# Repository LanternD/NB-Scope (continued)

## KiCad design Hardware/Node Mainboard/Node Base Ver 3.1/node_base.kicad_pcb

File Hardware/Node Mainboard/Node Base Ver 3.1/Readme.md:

Impoartant Note: Ver 3.1 is deprecated. 

Please generate the BOM by yourself if you want to use it.

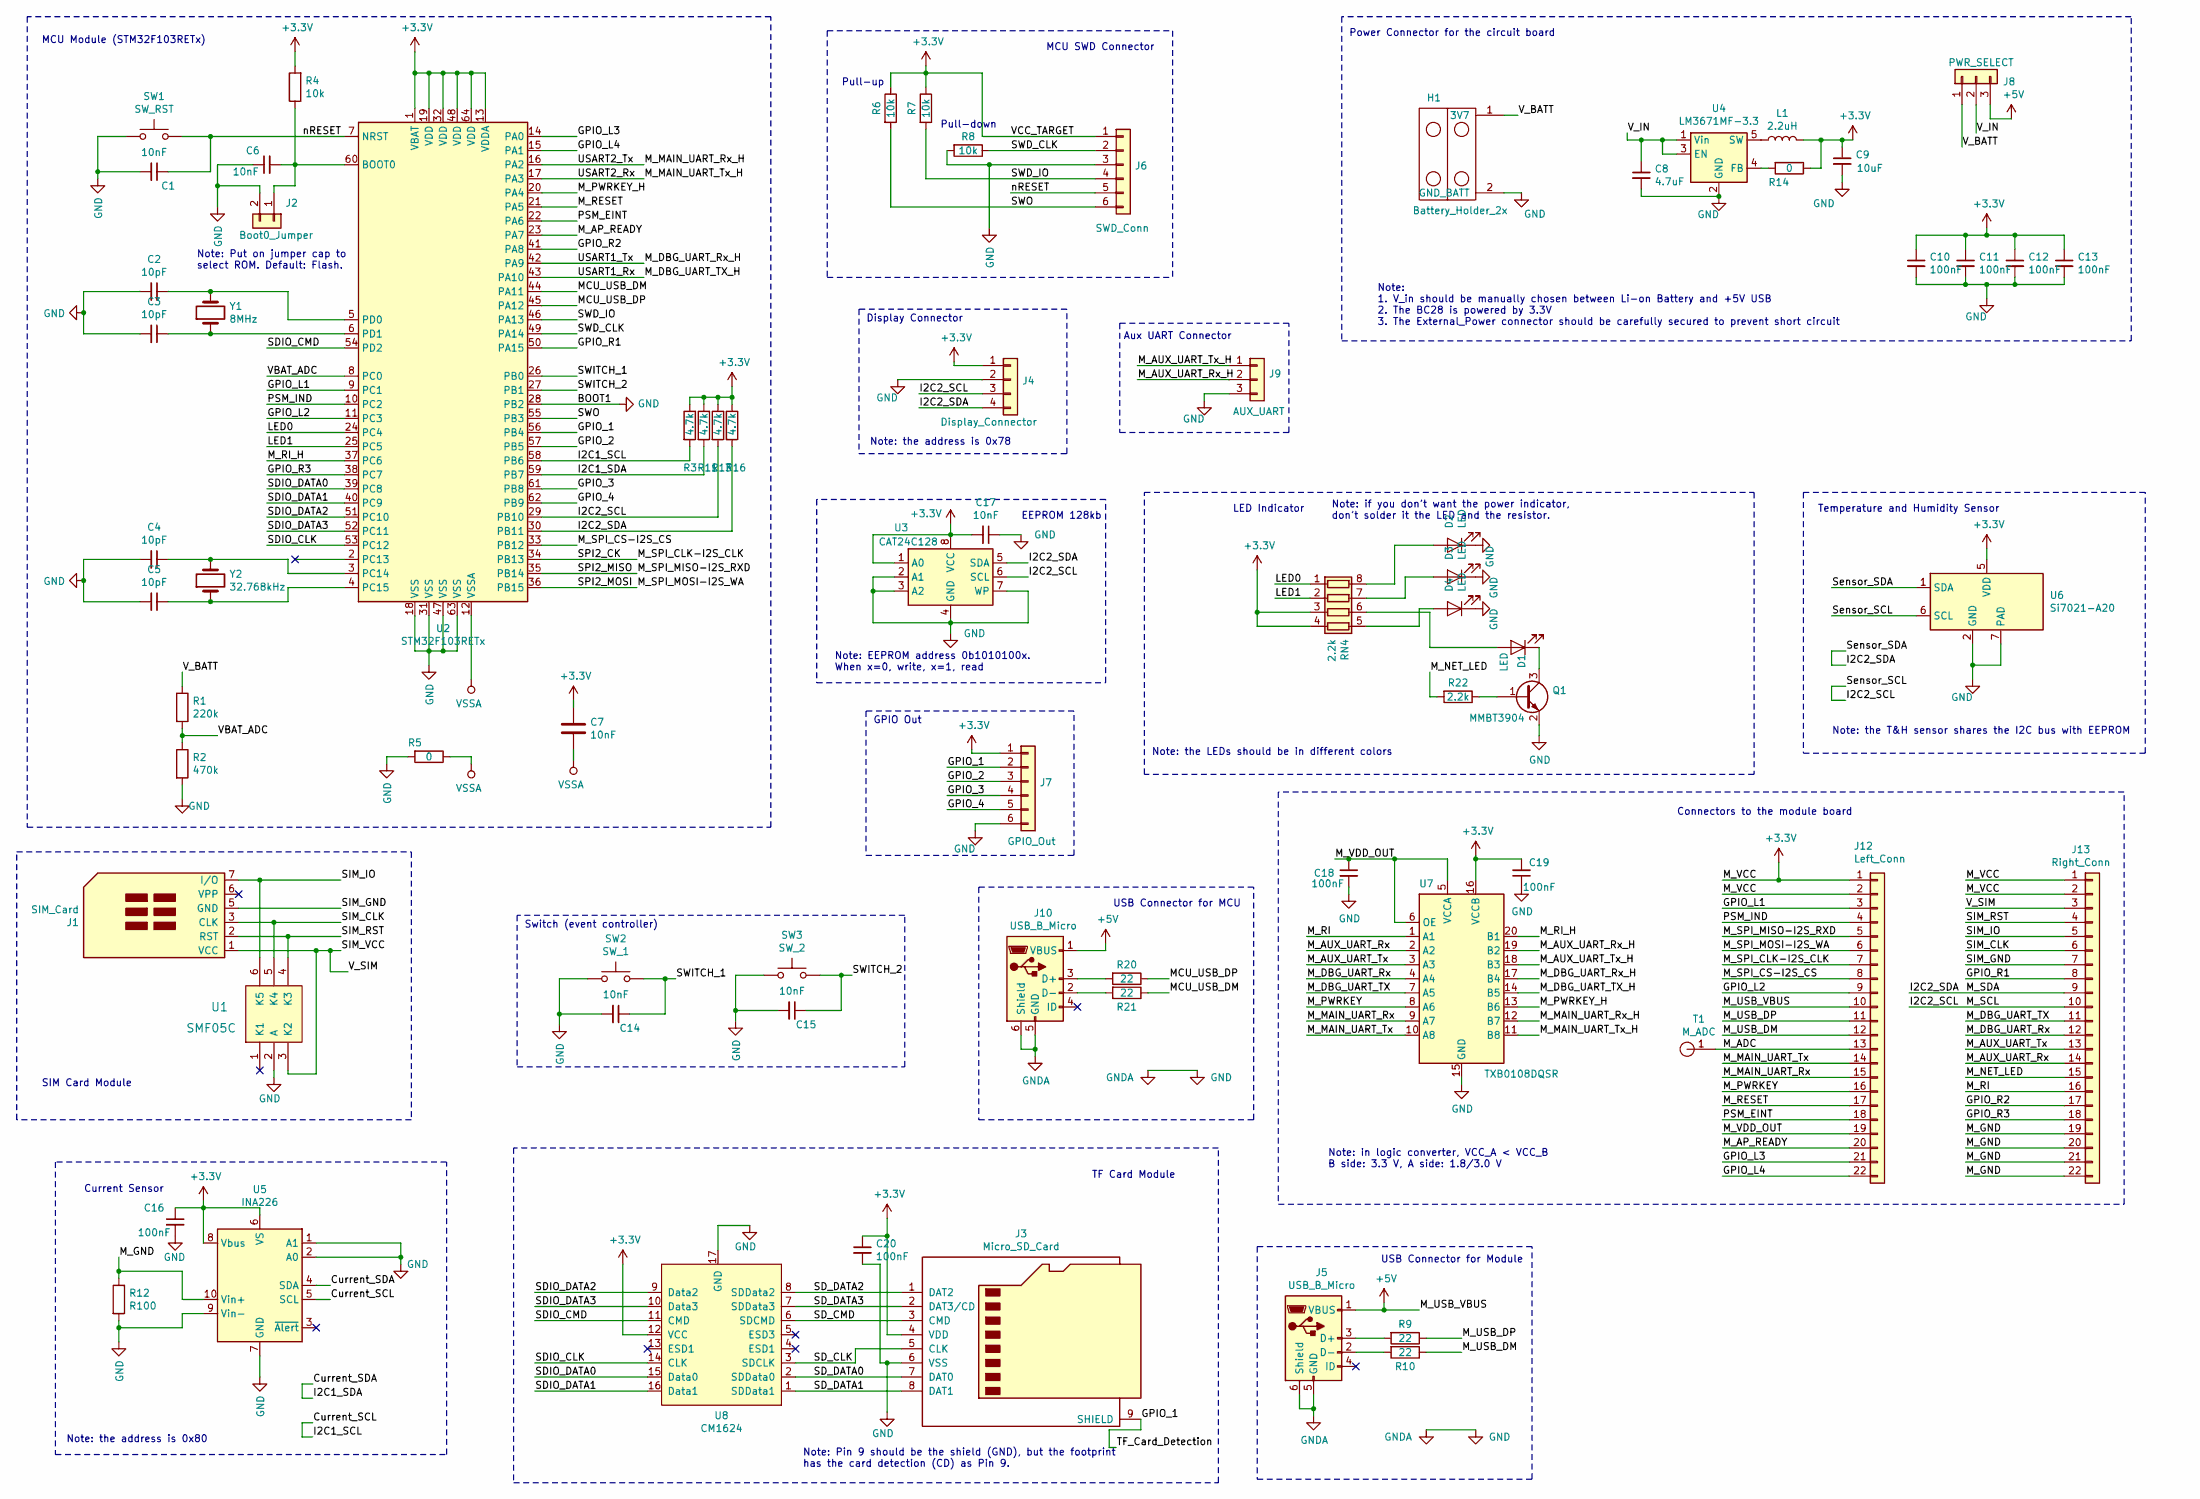
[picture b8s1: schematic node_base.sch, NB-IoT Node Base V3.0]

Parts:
C1, C6, C7, C14, C15, C17: 10nF; C_0603_1608Metric
C2, C3, C4, C5: 10pF; C_0603_1608Metric
C8: 4.7uF; C_0805_2012Metric
C9: 10uF; C_0805_2012Metric
C10, C11, C12, C13, C16, C18, C19, C20: 100nF; C_0603_1608Metric
D1, D2, D3, D4: LED; LED_0805_2012Metric
H1: Battery_Holder_2x; 18650_Battery_Holder_2x
J1: SIM_Card; Nano Sim Socket 1.1H, 6P
J2: Boot0_Jumper; PinHeader_1x02_P1.27mm_Vertical
J3: Micro_SD_Card; TF_Card_Socket
J4: Display_Connector; PinSocket_1x04_P1.27mm_Vertical
J5, J10: USB_B_Micro; USB_Micro-B_Molex-105017-0001
J6: SWD_Conn; PinSocket_1x06_P1.27mm_Vertical
J7: GPIO_Out; PinSocket_1x06_P1.27mm_Vertical
J8: PWR_SELECT; PinHeader_1x03_P2.54mm_Vertical
J9: AUX_UART; PinSocket_1x03_P1.27mm_Vertical
J12: Left_Conn; PinHeader_1x22_P1.27mm_Vertical
J13: Right_Conn; PinHeader_1x22_P1.27mm_Vertical
L1: 2.2uH; L_Sumida_CDRH2D14_3.2x3.2x1.55mm
Q1: MMBT3904; SOT-23
R1: 220k; R_0603_1608Metric
R2: 470k; R_0603_1608Metric
R3, R11, R13, R16: 4.7k; R_0603_1608Metric
R4, R6, R7, R8: 10k; R_0603_1608Metric
R5, R14: 0; R_0603_1608Metric
R9, R10, R20, R21: 22; R_0603_1608Metric
R12: R100; R_1206_3216Metric
R22: 2.2k; R_0603_1608Metric_Pad1.05x0.95mm_HandSolder
RN4: 2.2k; R_Array_Convex_4x0603
SW1: SW_RST; SW_SPST_FSMSM
SW2: SW_1; SW_SPST_FSMSM
SW3: SW_2; SW_SPST_FSMSM
T1: M_ADC; test_pad
U1: SMF05C
U2: STM32F103RETx; LQFP-64_10x10mm_P0.5mm
U3: CAT24C128; SOIC-8_3.9x4.9mm_P1.27mm
U4: LM3671MF-3.3; TSOT-23-5
U5: INA226; VSSOP-10_3x3mm_P0.5mm
U6: Si7021-A20; DFN-6-1EP_3x3mm_P1mm_EP1.5x2.4mm
U7: TXB0108DQSR; USON-20_2x4mm_P0.4mm
U8: CM1624; UDFN-16_3.3x1.35mm_0.4Pitch
Y1: 8MHz; Crystal_SMD_5032-2Pin_5.0x3.2mm
Y2: 32.768kHz; Crystal_SMD_3215-2Pin_3.2x1.5mm

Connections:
+3V3: C7.1, C9.1, C10.1, C11.1, C12.1, C13.1, C16.1, C17.2, C19.2, C20.1, J3.4 (VDD), J4.1, J6.1, J7.1, J12.1, J12.2, J13.1, J13.2, L1.2, R3.1, R4.2, R6.1, R7.1, R11.1, R13.1, R14.1, R16.1, RN4.3 (R3.1), RN4.4 (R4.1), U2.1 (VBAT), U2.13 (VDDA), U2.19 (VDD), U2.32 (VDD), U2.48 (VDD), U2.64 (VDD), U3.1 (A0), U3.8 (VCC), U5.6 (VS), U5.8 (Vbus), U6.5 (VDD), U7.16 (VCCB), U8.12 (VCC)
+5V: J5.1 (VBUS), J8.3, J10.1 (VBUS), J12.10
/Current_SCL: R3.2, U2.58 (PB6), U5.5 (SCL)
/Current_SDA: R11.2, U2.59 (PB7), U5.4 (SDA)
/GPIO_1: J3.9 (SHIELD), J7.2, U2.56 (PB4)
/GPIO_2: J7.3, U2.57 (PB5)
/GPIO_3: J7.4, U2.61 (PB8)
/GPIO_4: J7.5, U2.62 (PB9)
/GPIO_L1: J12.3, U2.9 (PC1)
/GPIO_L2: J12.9, U2.11 (PC3)
/GPIO_L3: J12.21, U2.14 (PA0)
/GPIO_L4: J12.22, U2.15 (PA1)
/GPIO_R1: J13.8, U2.50 (PA15)
/GPIO_R2: J13.17, U2.41 (PA8)
/GPIO_R3: J13.18, U2.38 (PC7)
/I2C2_SCL: J4.3, J13.10, R13.2, U2.29 (PB10), U3.6 (SCL), U6.6 (SCL)
/I2C2_SDA: J4.4, J13.9, R16.2, U2.30 (PB11), U3.5 (SDA), U6.1 (SDA)
/LED0: RN4.1 (R1.1), U2.24 (PC4)
/LED1: RN4.2 (R2.1), U2.25 (PC5)
/MCU_USB_DM: R21.1, U2.44 (PA11)
/MCU_USB_DP: R20.1, U2.45 (PA12)
/M_ADC: J12.13, T1.1
/M_AP_READY: J12.20, U2.23 (PA7)
/M_AUX_UART_Rx: J13.14, U7.2 (A2)
/M_AUX_UART_Rx_H: J9.2, U7.19 (B2)
/M_AUX_UART_Tx: J13.13, U7.3 (A3)
/M_AUX_UART_Tx_H: J9.1, U7.18 (B3)
/M_DBG_UART_Rx: J13.12, U7.4 (A4)
/M_DBG_UART_Rx_H: U2.42 (PA9), U7.17 (B4)
/M_DBG_UART_TX: J13.11, U7.7 (A5)
/M_DBG_UART_TX_H: U2.43 (PA10), U7.14 (B5)
/M_GND: J13.19, J13.20, J13.21, J13.22, R12.1, U5.10 (Vin+)
/M_MAIN_UART_Rx: J12.15, U7.9 (A7)
/M_MAIN_UART_Rx_H: U2.16 (PA2), U7.12 (B7)
/M_MAIN_UART_Tx: J12.14, U7.10 (A8)
/M_MAIN_UART_Tx_H: U2.17 (PA3), U7.11 (B8)
/M_NET_LED: J13.15, R22.2
/M_PWRKEY: J12.16, U7.8 (A6)
/M_PWRKEY_H: U2.20 (PA4), U7.13 (B6)
/M_RESET: J12.17, U2.21 (PA5)
/M_RI: J13.16, U7.1 (A1)
/M_RI_H: U2.37 (PC6), U7.20 (B1)
/M_SPI_CLK-I2S_CLK: J12.7, U2.34 (PB13)
/M_SPI_CS-I2S_CS: J12.8, U2.33 (PB12)
/M_SPI_MISO-I2S_RXD: J12.5, U2.35 (PB14)
/M_SPI_MOSI-I2S_WA: J12.6, U2.36 (PB15)
/M_USB_DM: J12.12, R10.1
/M_USB_DP: J12.11, R9.1
/M_VDD_OUT: C18.1, J12.19, U7.5 (VCCA), U7.6 (OE)
/PSM_EINT: J12.18, U2.22 (PA6)
/PSM_IND: J12.4, U2.10 (PC2)
/SDIO_CLK: U2.53 (PC12), U8.14 (CLK)
/SDIO_CMD: U2.54 (PD2), U8.11 (CMD)
/SDIO_DATA0: U2.39 (PC8), U8.15 (Data0)
/SDIO_DATA1: U2.40 (PC9), U8.16 (Data1)
/SDIO_DATA2: U2.51 (PC10), U8.9 (Data2)
/SDIO_DATA3: U2.52 (PC11), U8.10 (Data3)
/SD_CLK: J3.5 (CLK), U8.3 (SDCLK)
/SD_CMD: J3.3 (CMD), U8.6 (SDCMD)
/SD_DATA0: J3.7 (DAT0), U8.2 (SDData0)
/SD_DATA1: J3.8 (DAT1), U8.1 (SDData1)
/SD_DATA2: J3.1 (DAT2), U8.8 (SDData2)
/SD_DATA3: J3.2 (DAT3/CD), U8.7 (SDData3)
/SIM_CLK: J1.3 (CLK), J13.6, U1.5 (K4)
/SIM_GND: J1.5 (GND), J13.7
/SIM_IO: J1.7 (I/O), J13.5, U1.6 (K5)
/SIM_RST: J1.2 (RST), J13.4, U1.4 (K3)
/SIM_VCC: J1.1 (VCC), J13.3, U1.3 (K2)
/SWD_CLK: J6.2, R8.1, U2.49 (PA14)
/SWD_IO: J6.4, R7.2, U2.46 (PA13)
/SWITCH_1: C14.1, SW2.2, U2.26 (PB0)
/SWITCH_2: C15.1, SW3.2, U2.27 (PB1)
/SWO: J6.6, R6.2, U2.55 (PB3)
/VBAT_ADC: R1.2, R2.1, U2.8 (PC0)
/V_BATT: H1.1 (3V7), J8.1, R1.1
/V_IN: C8.1, J8.2, U4.1 (Vin), U4.3 (EN)
/nRESET: C1.1, J6.5, SW1.2, U2.7 (NRST)
GND: C1.2, C2.2, C3.2, C4.2, C5.2, C6.1, C8.2, C9.2, C10.2, C11.2, C12.2, C13.2, C14.2, C15.2, C16.2, C17.1, C18.2, C19.1, C20.2, D2.1 (K), D3.1 (K), D4.1 (K), H1.2 (GND_BATT), J2.2, J3.6 (VSS), J4.2, J5.5 (GND), J5.6 (Shield), J6.3, J7.6, J9.3, J10.5 (GND), J10.6 (Shield), Q1.2 (E), R2.2, R5.2, R8.2, R12.2, SW1.1, SW2.1, SW3.1, U1.2 (A), U2.18 (VSS), U2.28 (PB2), U2.31 (VSS), U2.47 (VSS), U2.63 (VSS), U3.2 (A1), U3.3 (A2), U3.4 (GND), U3.7 (WP), U4.2 (GND), U5.1 (A1), U5.2 (A0), U5.7 (GND), U5.9 (Vin-), U6.2 (GND), U6.7 (PAD), U7.15 (GND), U8.17 (GND)
unnamed: C2.1, U2.5 (PD0), Y1.2
unnamed: C3.1, U2.6 (PD1), Y1.1
unnamed: C4.1, U2.3 (PC14), Y2.2
unnamed: C5.1, U2.4 (PC15), Y2.1
unnamed: C6.2, J2.1, R4.1, U2.60 (BOOT0)
unnamed: D1.1 (K), Q1.3 (C)
unnamed: D1.2 (A), RN4.6 (R3.2)
unnamed: D2.2 (A), RN4.8 (R1.2)
unnamed: D3.2 (A), RN4.7 (R2.2)
unnamed: D4.2 (A), RN4.5 (R4.2)
unnamed: J5.2 (D-), R10.2
unnamed: J5.3 (D+), R9.2
unnamed: J10.2 (D-), R21.2
unnamed: J10.3 (D+), R20.2
unnamed: L1.1, U4.5 (SW)
unnamed: Q1.1 (B), R22.1
unnamed: R14.2, U4.4 (FB)
VSSA: C7.2, R5.1, U2.12 (VSSA)

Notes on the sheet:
Note: Put on jumper cap to select ROM. Default: Flash.
MCU Module (STM32F103RETx)
Power Connector for the circuit board
Note: 1. V_in should be manually chosen between Li-on Battery and +5V USB 2. The BC28 is powered by 3.3V 3. The External_Power connector should be carefully secured to prevent short circuit
Pull-down
Pull-up
MCU SWD Connector
EEPROM 128kb
Note: the LEDs should be in different colors
LED Indicator
Note: if you don’t want the power indicator, don’t solder it the LED and the resistor.
Note: the T&H sensor shares the I2C bus with EEPROM
Connectors to the module board
Current Sensor
SIM Card Module
Temperature and Humidity Sensor
Switch (event controller)
Note: Pin 9 should be the shield (GND), but the footprint has the card detection (CD) as Pin 9.
TF Card Module
Note: EEPROM address 0b1010100x. When x=0, write, x=1, read
Display Connector
Note: the address is 0x78
Note: the address is 0x80
Aux UART Connector
USB Connector for MCU
USB Connector for Module
GPIO Out
Note: in logic converter, VCC_A < VCC_B B side: 3.3 V, A side: 1.8/3.0 V

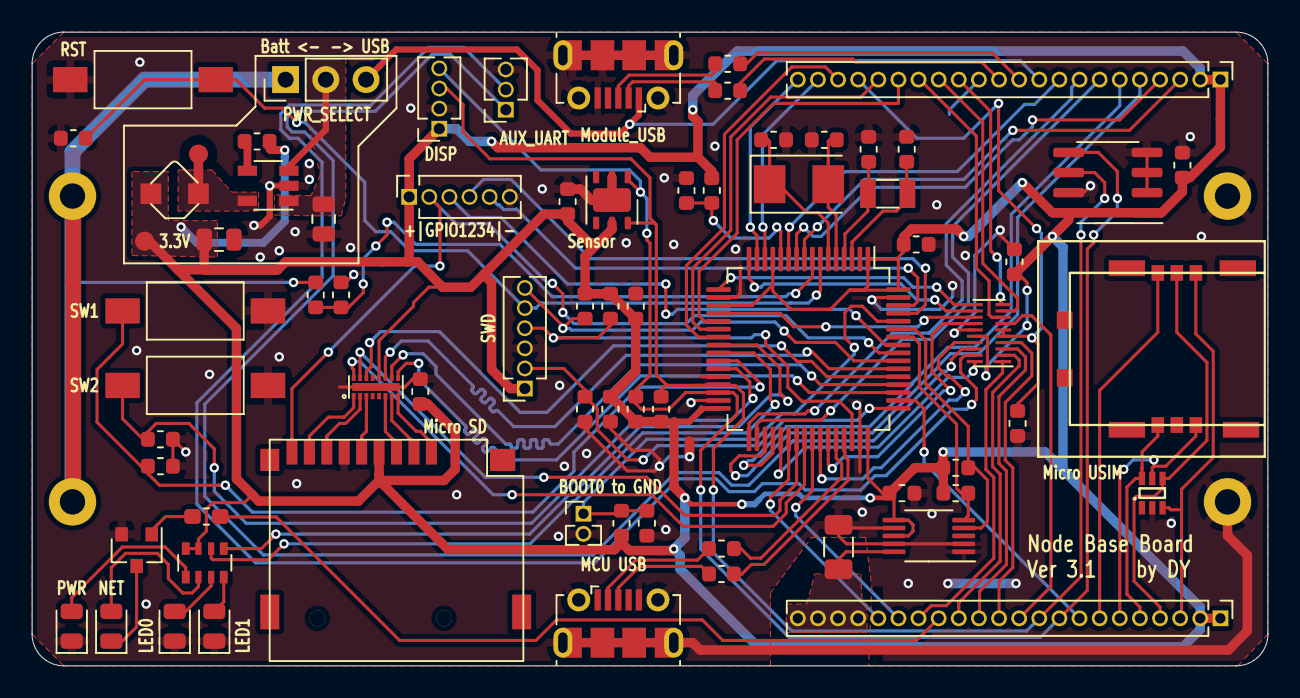
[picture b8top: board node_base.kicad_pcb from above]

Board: 2 copper layers, 78.0 x 40.0 mm, 72 parts (1 on the bottom side), 96 nets.

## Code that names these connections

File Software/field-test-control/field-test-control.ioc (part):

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Mcu.Name=STM32F103R(C-D-E)Tx
Mcu.Package=LQFP64
Mcu.UserName=STM32F103RETx
PA0-WKUP.GPIOParameters=GPIO_Label
PA0-WKUP.GPIO_Label=M_GPIO_L3
PA0-WKUP.Signal=GPIO_Output
PA1.GPIOParameters=GPIO_PuPd,GPIO_Label
PA1.GPIO_Label=M_GPIO_L4
PA1.GPIO_PuPd=GPIO_NOPULL
PA1.Signal=GPIO_Output
PA10.Mode=Asynchronous
PA10.Signal=USART1_RX
PA11.Mode=Device
PA11.Signal=USB_DM
PA12.Mode=Device
PA12.Signal=USB_DP
PA13.Mode=Serial_Wire
PA13.Signal=SYS_JTMS-SWDIO
PA14.Mode=Serial_Wire
PA14.Signal=SYS_JTCK-SWCLK
PA15.GPIOParameters=GPIO_Label
PA15.GPIO_Label=M_GPIO_R1
PA15.Signal=GPIO_Output
PA2.Mode=Asynchronous
PA2.Signal=USART2_TX
PA3.Mode=Asynchronous
PA3.Signal=USART2_RX
PA4.GPIOParameters=PinState,GPIO_PuPd,GPIO_Label
PA4.GPIO_Label=M_PWRKEY
PA4.GPIO_PuPd=GPIO_PULLUP
PA4.PinState=GPIO_PIN_RESET
PA4.Signal=GPIO_Output
PA5.GPIOParameters=GPIO_PuPd,GPIO_Label
PA5.GPIO_Label=M_RESET
PA5.GPIO_PuPd=GPIO_PULLUP
PA5.Signal=GPIO_Output
PA6.GPIOParameters=GPIO_Label
PA6.GPIO_Label=M_WAKEUP_FROM_PSM
PA6.Signal=GPIO_Output
PA7.GPIOParameters=GPIO_Label
PA7.GPIO_Label=M_AP_READY
PA7.Signal=GPIO_Output
PA8.GPIOParameters=GPIO_Label
PA8.GPIO_Label=M_GPIO_R2
PA8.Signal=GPIO_Output
PA9.Mode=Asynchronous
PA9.Signal=USART1_TX
PB0.GPIOParameters=GPIO_PuPd,GPIO_Label,GPIO_ModeDefaultEXTI
PB0.GPIO_Label=BUTTON1
PB0.GPIO_ModeDefaultEXTI=GPIO_MODE_IT_FALLING
PB0.GPIO_PuPd=GPIO_PULLUP
PB0.Signal=GPXTI0
PB1.GPIOParameters=GPIO_PuPd,GPIO_Label,GPIO_ModeDefaultEXTI
PB1.GPIO_Label=BUTTON2
PB1.GPIO_ModeDefaultEXTI=GPIO_MODE_IT_FALLING
PB1.GPIO_PuPd=GPIO_PULLUP
PB1.Signal=GPXTI1
PB10.GPIOParameters=GPIO_Label
PB10.GPIO_Label=BUS_SCL
PB10.Mode=I2C
PB10.Signal=I2C2_SCL
PB11.GPIOParameters=GPIO_Label
PB11.GPIO_Label=BUS_SDA
PB11.Mode=I2C
PB11.Signal=I2C2_SDA
PB12.GPIOParameters=GPIO_Label
PB12.GPIO_Label=M_SPI_CS
PB12.Signal=GPIO_Output
PB13.Mode=Full_Duplex_Master
PB13.Signal=SPI2_SCK
PB14.Mode=Full_Duplex_Master
PB14.Signal=SPI2_MISO
PB15.Mode=Full_Duplex_Master
PB15.Signal=SPI2_MOSI
PB3.Signal=SYS_JTDO-TRACESWO
PB4.GPIOParameters=GPIO_Label
PB4.GPIO_Label=TF_DET
PB4.Signal=GPIO_Input
PB5.GPIOParameters=GPIO_Label
PB5.GPIO_Label=GPIO_2
PB5.Signal=GPIO_Output
PB6.GPIOParameters=GPIO_Label
PB6.GPIO_Label=INA226_SCL
PB6.Mode=I2C
PB6.Signal=I2C1_SCL
PB7.GPIOParameters=GPIO_Label
PB7.GPIO_Label=INA226_SDA
PB7.Mode=I2C
PB7.Signal=I2C1_SDA
PB8.GPIOParameters=GPIO_Label
PB8.GPIO_Label=GPIO_3
PB8.Signal=GPIO_Output
PB9.GPIOParameters=GPIO_Label
PB9.GPIO_Label=GPIO_4
PB9.Signal=GPIO_Output
PC0.GPIOParameters=GPIO_Label
PC0.GPIO_Label=V_BATT_ADC
PC0.Signal=ADCx_IN10
PC1.GPIOParameters=GPIO_Label
PC1.GPIO_Label=M_GPIO_L1
PC1.Signal=GPIO_Output
PC10.Mode=SD_4_bits_Wide_bus
PC10.Signal=SDIO_D2
PC11.Mode=SD_4_bits_Wide_bus
PC11.Signal=SDIO_D3
PC12.Mode=SD_4_bits_Wide_bus
PC12.Signal=SDIO_CK
PC14-OSC32_IN.Mode=LSE-External-Oscillator
PC14-OSC32_IN.Signal=RCC_OSC32_IN
PC15-OSC32_OUT.Mode=LSE-External-Oscillator
PC15-OSC32_OUT.Signal=RCC_OSC32_OUT
PC2.GPIOParameters=GPIO_Label
PC2.GPIO_Label=M_PSM_IND
PC2.Signal=GPIO_Input
PC3.GPIOParameters=GPIO_Label
PC3.GPIO_Label=M_GPIO_L2
PC3.Signal=GPIO_Output
PC4.GPIOParameters=GPIO_Label
PC4.GPIO_Label=LED0
PC4.Signal=GPIO_Output
PC5.GPIOParameters=GPIO_Label
PC5.GPIO_Label=LED1
PC5.Signal=GPIO_Output
PC6.GPIOParameters=GPIO_Label
PC6.GPIO_Label=M_RI
PC6.Signal=GPIO_Input
PC7.GPIOParameters=GPIO_Label
PC7.GPIO_Label=M_GPIO_R3
PC7.Signal=GPIO_Output
PC8.Mode=SD_4_bits_Wide_bus
PC8.Signal=SDIO_D0
PC9.Mode=SD_4_bits_Wide_bus
PC9.Signal=SDIO_D1
PD0-OSC_IN.Mode=HSE-External-Oscillator
PD0-OSC_IN.Signal=RCC_OSC_IN
PD1-OSC_OUT.Mode=HSE-External-Oscillator
PD1-OSC_OUT.Signal=RCC_OSC_OUT
PD2.Mode=SD_4_bits_Wide_bus
PD2.Signal=SDIO_CMD
RCC.SYSCLKFreq_VALUE=72000000
RCC.SYSCLKSource=RCC_SYSCLKSOURCE_PLLCLK
board=custom

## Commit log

2020-09-02 Initial commit, add hardware designs
2020-09-06 Add more description in NB-Scope
2020-09-07 Added assets and updated hardware readme
2020-09-07 Move all the photos to assets brach
2020-09-07 Test Readme image link update
2020-09-07 Reverse the changes in hardware readme
2020-09-07 add readme to node mainboard
2020-09-07 add pic: module board pin assignment
2020-09-07 fixed repo structure
2020-09-07 removed assets folder in master branch
2020-09-08 Update mainboard readme.
2020-09-08 Fixed picture links
2020-09-08 Added materials, updated readme
2020-09-08 Added ver 3.1 photos
2020-09-08 Added software folder, updated aux board readme
2020-09-08 add pic: current calibration guide
2020-09-08 updated aux readme
2020-09-08 Updated the hardware mainboard readme
2020-09-08 added udp server code
2020-09-08 organized software code base
2020-09-24 add field test control readme
2022-01-25 Uploaded software codes
